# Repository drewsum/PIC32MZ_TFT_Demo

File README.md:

# PIC32MZ_TFT_Demo
Custom demo board for controlling a TFT screen using PIC32MZ

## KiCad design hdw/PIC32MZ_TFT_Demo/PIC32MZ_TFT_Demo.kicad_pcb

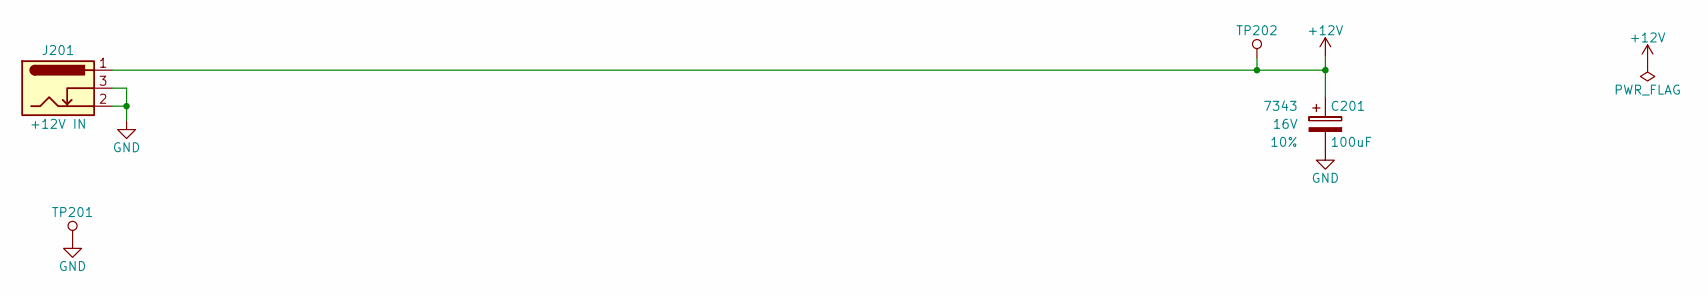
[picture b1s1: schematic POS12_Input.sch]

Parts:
C201: 100uF; CP_Tantalum_Case-X_EIA-7343-43_Reflow; Voltage 16V; Tolerance 10%; Digi-Key PN 718-1102-1-ND
J201: +12V IN; BARREL_JACK
TP201: TP; Pin_Header_Angled_1x01_Pitch2.54mm
TP202: TP; Test_Point

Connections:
+12V: C201.1, J201.1, TP202.1; also elsewhere on the board
GND: C201.2, J201.2, J201.3, TP201.1; also elsewhere on the board

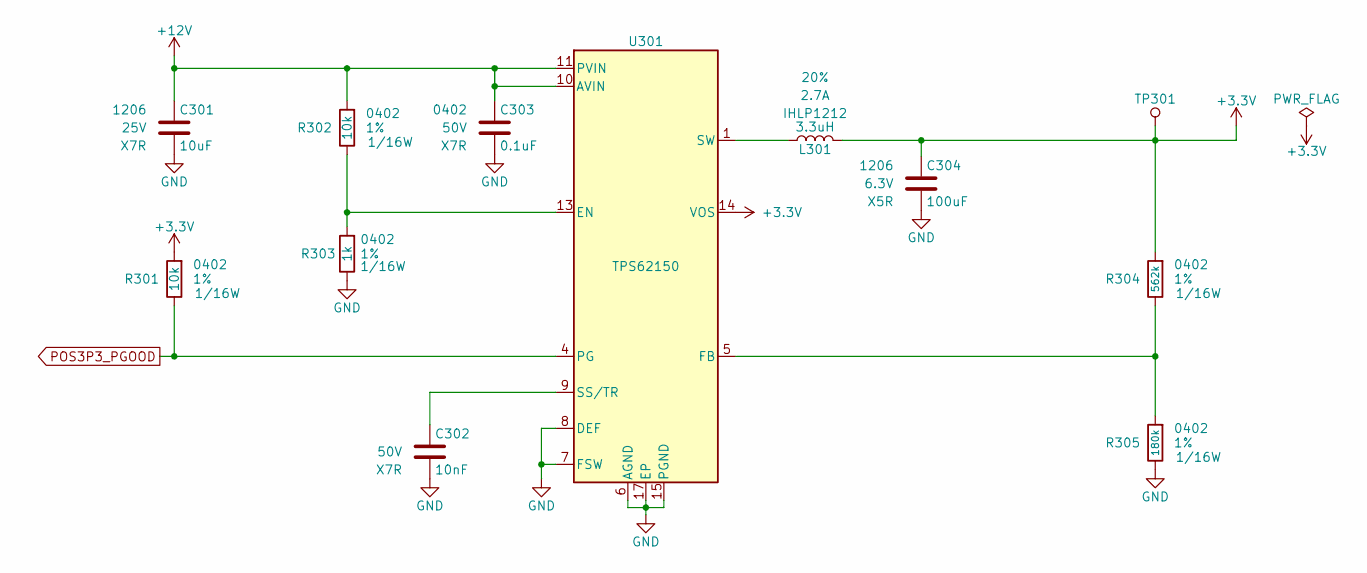
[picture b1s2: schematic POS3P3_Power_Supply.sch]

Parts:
C301: 10uF; C_1206; Voltage 25V; Digi-Key PN 1276-7031-1-ND
C302: 10nF; C_0402; Voltage 50V; Digi-Key PN 490-13295-1-ND
C303: 0.1uF; C_0402; Voltage 50V; Digi-Key PN 490-10701-1-ND
C304: 100uF; C_1206; Voltage 6.3V; Digi-Key PN 587-1963-1-ND
L301: 3.3uH; L_Vishay_IHLP-1212; Tolerance 20%; Digi-Key PN 541-2567-1-ND
R301, R302: 10k; R_0402; Tolerance 1%; Digi-Key PN RMCF0402FT10K0CT-ND
R303: 1k; R_0402; Tolerance 1%; Digi-Key PN 541-1.00KLCT-ND
R304: 562k; R_0402; Tolerance 1%; Digi-Key PN 311-562KLRCT-ND
R305: 180k; R_0402; Tolerance 1%; Digi-Key PN A129654CT-ND
TP301: TP; Test_Point
U301: TPS62150; QFN-16-1EP_3x3mm_P0.5mm_EP1.8x1.8mm; Digi-Key PN 296-41757-1-ND

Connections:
+3V3: C304.1, L301.2, R301.1, R304.1, TP301.1, U301.14 (VOS); also elsewhere on the board
+12V: C301.1, C303.1, R302.1, U301.10 (AVIN), U301.11 (PVIN), U301.12 (PVIN); also elsewhere on the board
GND: C301.2, C302.2, C303.2, C304.2, R303.2, R305.2, U301.6 (AGND), U301.7 (FSW), U301.8 (DEF), U301.15 (PGND), U301.16 (PGND), U301.17 (EP); also elsewhere on the board
unnamed: C302.1, U301.9 (SS/TR)
unnamed: L301.1, U301.1 (SW), U301.2 (SW), U301.3 (SW)
unnamed: R302.2, R303.1, U301.13 (EN)
unnamed: R304.2, R305.1, U301.5 (FB)
POS3P3_PGOOD: R301.2, U301.4 (PG); also elsewhere on the board

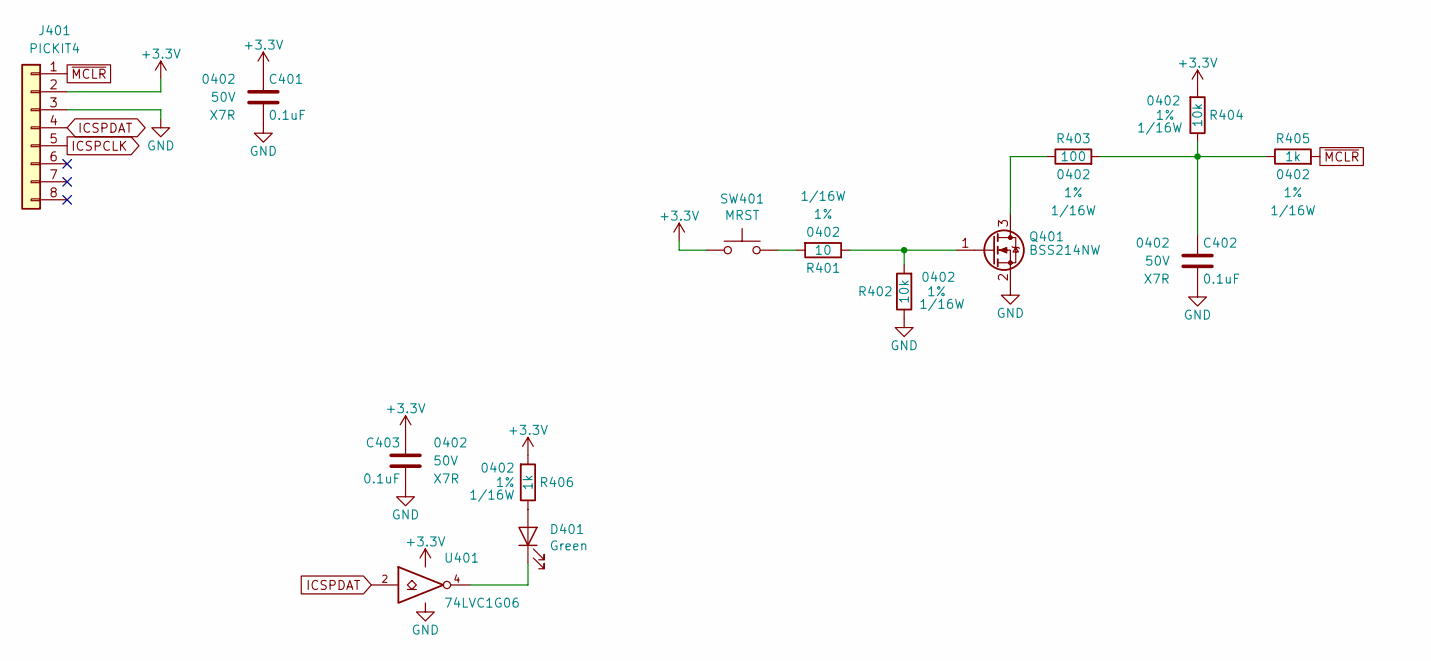
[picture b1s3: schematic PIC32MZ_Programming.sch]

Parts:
C401, C402, C403: 0.1uF; C_0402; Voltage 50V; Digi-Key PN 490-10701-1-ND
D401: Green; LED_0402; Digi-Key PN 1497-1219-1-ND
J401: PICKIT4; PICKIT4_Header
Q401: BSS214NW; SOT-323_SC-70; Digi-Key PN BSS214NWH6327XTSA1CT-ND
R401: 10; R_0402; Tolerance 1%; Digi-Key PN 541-3964-1-ND
R402, R404: 10k; R_0402; Tolerance 1%; Digi-Key PN RMCF0402FT10K0CT-ND
R403: 100; R_0402; Tolerance 1%; Digi-Key PN 541-100LCT-ND
R405, R406: 1k; R_0402; Tolerance 1%; Digi-Key PN 541-1.00KLCT-ND
SW401: MRST; SW_PUSH_6mm
U401: 74LVC1G06; SOT-353_SC-70-5; Digi-Key PN 296-8484-1-ND

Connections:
+3V3: C401.1, C403.1, J401.2, R404.1, R406.1, SW401.1, U401.5 (VCC); also elsewhere on the board
GND: C401.2, C402.2, C403.2, J401.3, Q401.2 (S), R402.2, U401.3 (GND); also elsewhere on the board
ICSPCLK: J401.5; also elsewhere on the board
ICSPDAT: J401.4, U401.2; also elsewhere on the board
unnamed: C402.1, R403.1, R404.2, R405.2
unnamed: D401.1 (K), U401.4
unnamed: D401.2 (A), R406.2
unnamed: Q401.1 (G), R401.2, R402.1
unnamed: Q401.3 (D), R403.2
unnamed: R401.1, SW401.2
~MCLR: J401.1, R405.1; also elsewhere on the board

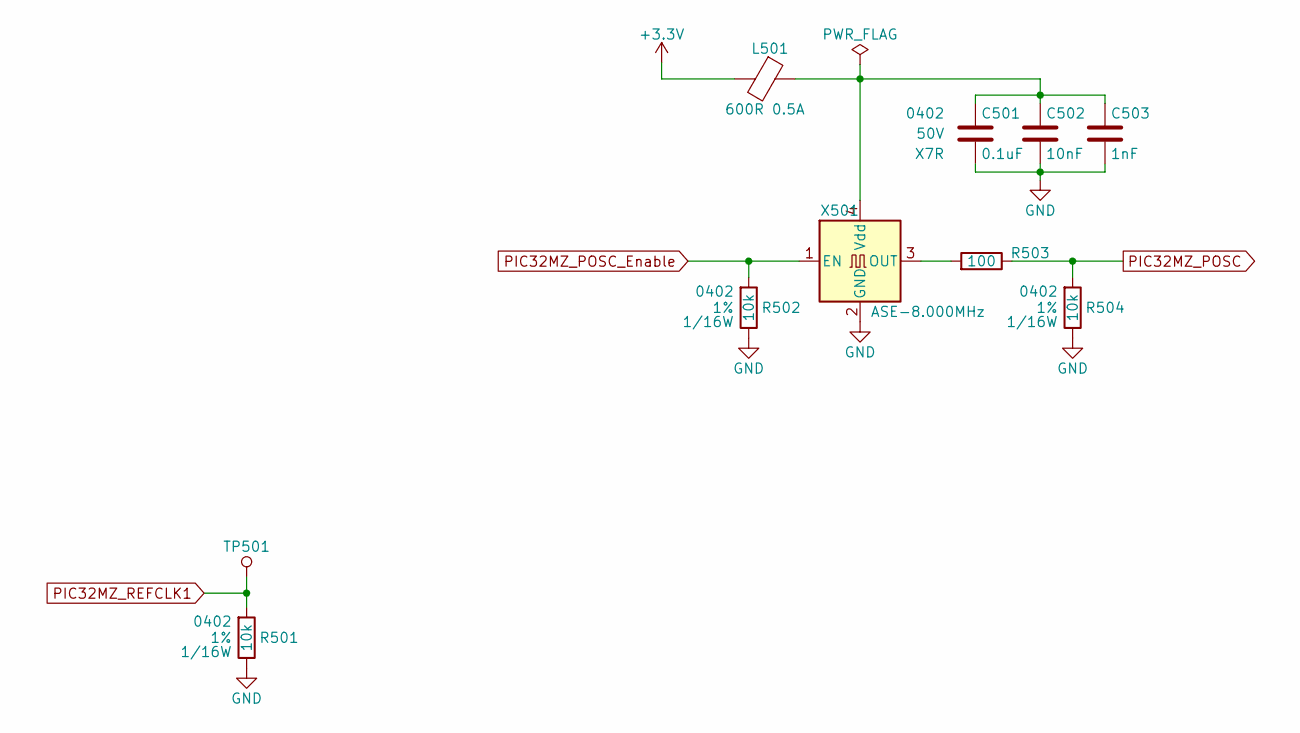
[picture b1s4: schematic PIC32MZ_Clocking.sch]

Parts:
C501: 0.1uF; C_0402; Voltage 50V; Digi-Key PN 490-10701-1-ND
C502: 10nF; C_0402; Voltage 50V; Digi-Key PN 490-13295-1-ND
C503: 1nF; C_0402; Voltage 50V; Digi-Key PN 399-1032-1-ND
L501: 600R 0.5A; L_0402; Digi-Key PN 490-5441-1-ND
R501, R502, R504: 10k; R_0402; Tolerance 1%; Digi-Key PN RMCF0402FT10K0CT-ND
R503: 100; R_0402; Tolerance 1%; Digi-Key PN 541-100LCT-ND
TP501: TP; Test_Point
X501: ASE-8.000MHz; Oscillator_SMD_Abracon_ASE-4Pin_3.2x2.5mm; Digi-Key PN 535-9558-1-ND

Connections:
+3V3: L501.2; also elsewhere on the board
GND: C501.2, C502.2, C503.2, R501.2, R502.2, R504.2, X501.2 (GND); also elsewhere on the board
unnamed: C501.1, C502.1, C503.1, L501.1, X501.4 (Vdd)
unnamed: R503.1, X501.3 (OUT)
PIC32MZ_POSC: R503.2, R504.1; also elsewhere on the board
PIC32MZ_POSC_Enable: R502.1, X501.1 (EN); also elsewhere on the board
PIC32MZ_REFCLK1: R501.1, TP501.1; also elsewhere on the board

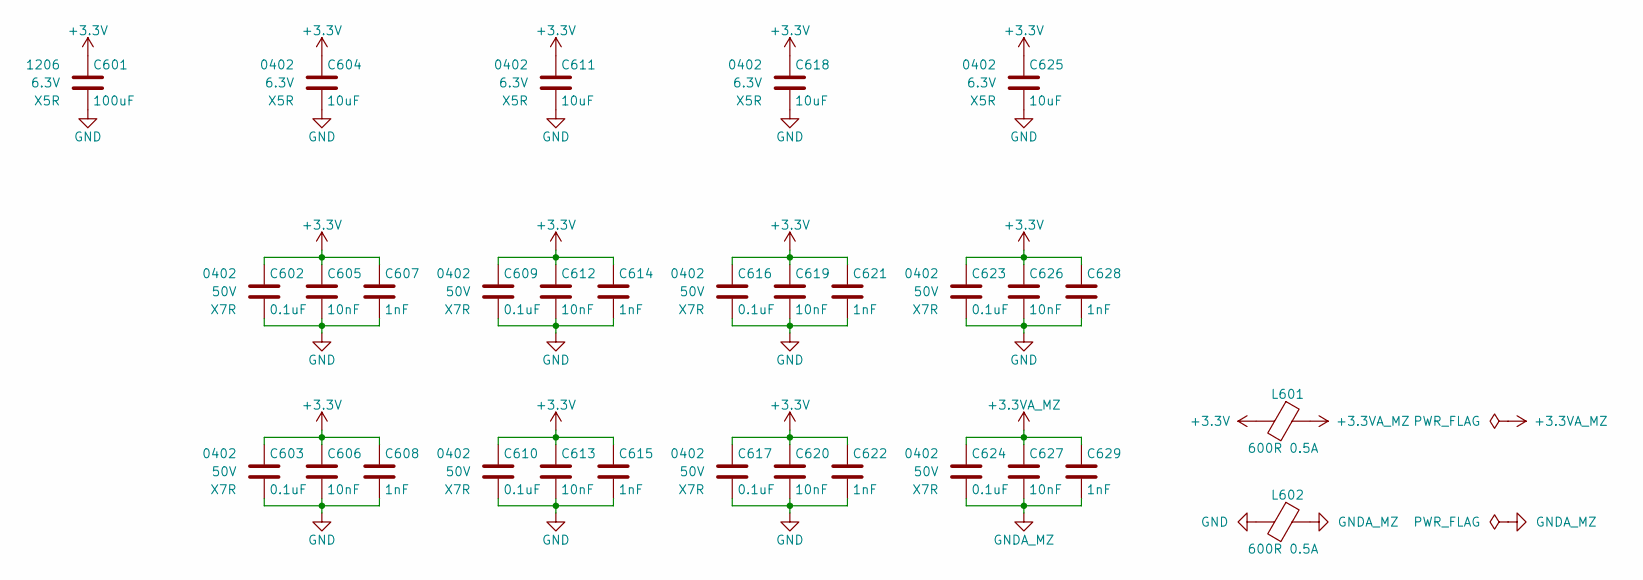
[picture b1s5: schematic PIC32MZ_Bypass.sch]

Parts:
C601: 100uF; C_1206; Voltage 6.3V; Digi-Key PN 587-1963-1-ND
C602, C603, C609, C610, C616, C617, C623, C624: 0.1uF; C_0402; Voltage 50V; Digi-Key PN 490-10701-1-ND
C604, C611, C618, C625: 10uF; C_0402; Voltage 6.3V; Digi-Key PN 490-13211-1-ND
C605, C606, C612, C613, C619, C620, C626, C627: 10nF; C_0402; Voltage 50V; Digi-Key PN 490-13295-1-ND
C607, C608, C614, C615, C621, C622, C628, C629: 1nF; C_0402; Voltage 50V; Digi-Key PN 399-1032-1-ND
L601, L602: 600R 0.5A; L_0402; Digi-Key PN 490-5441-1-ND

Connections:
+3.3VA_MZ: C624.1, C627.1, C629.1, L601.1; also elsewhere on the board
+3V3: C601.1, C602.1, C603.1, C604.1, C605.1, C606.1, C607.1, C608.1, C609.1, C610.1, C611.1, C612.1, C613.1, C614.1, C615.1, C616.1, C617.1, C618.1, C619.1, C620.1, C621.1, C622.1, C623.1, C625.1, C626.1, C628.1, L601.2; also elsewhere on the board
GND: C601.2, C602.2, C603.2, C604.2, C605.2, C606.2, C607.2, C608.2, C609.2, C610.2, C611.2, C612.2, C613.2, C614.2, C615.2, C616.2, C617.2, C618.2, C619.2, C620.2, C621.2, C622.2, C623.2, C625.2, C626.2, C628.2, L602.2; also elsewhere on the board
GNDA_MZ: C624.2, C627.2, C629.2, L602.1; also elsewhere on the board

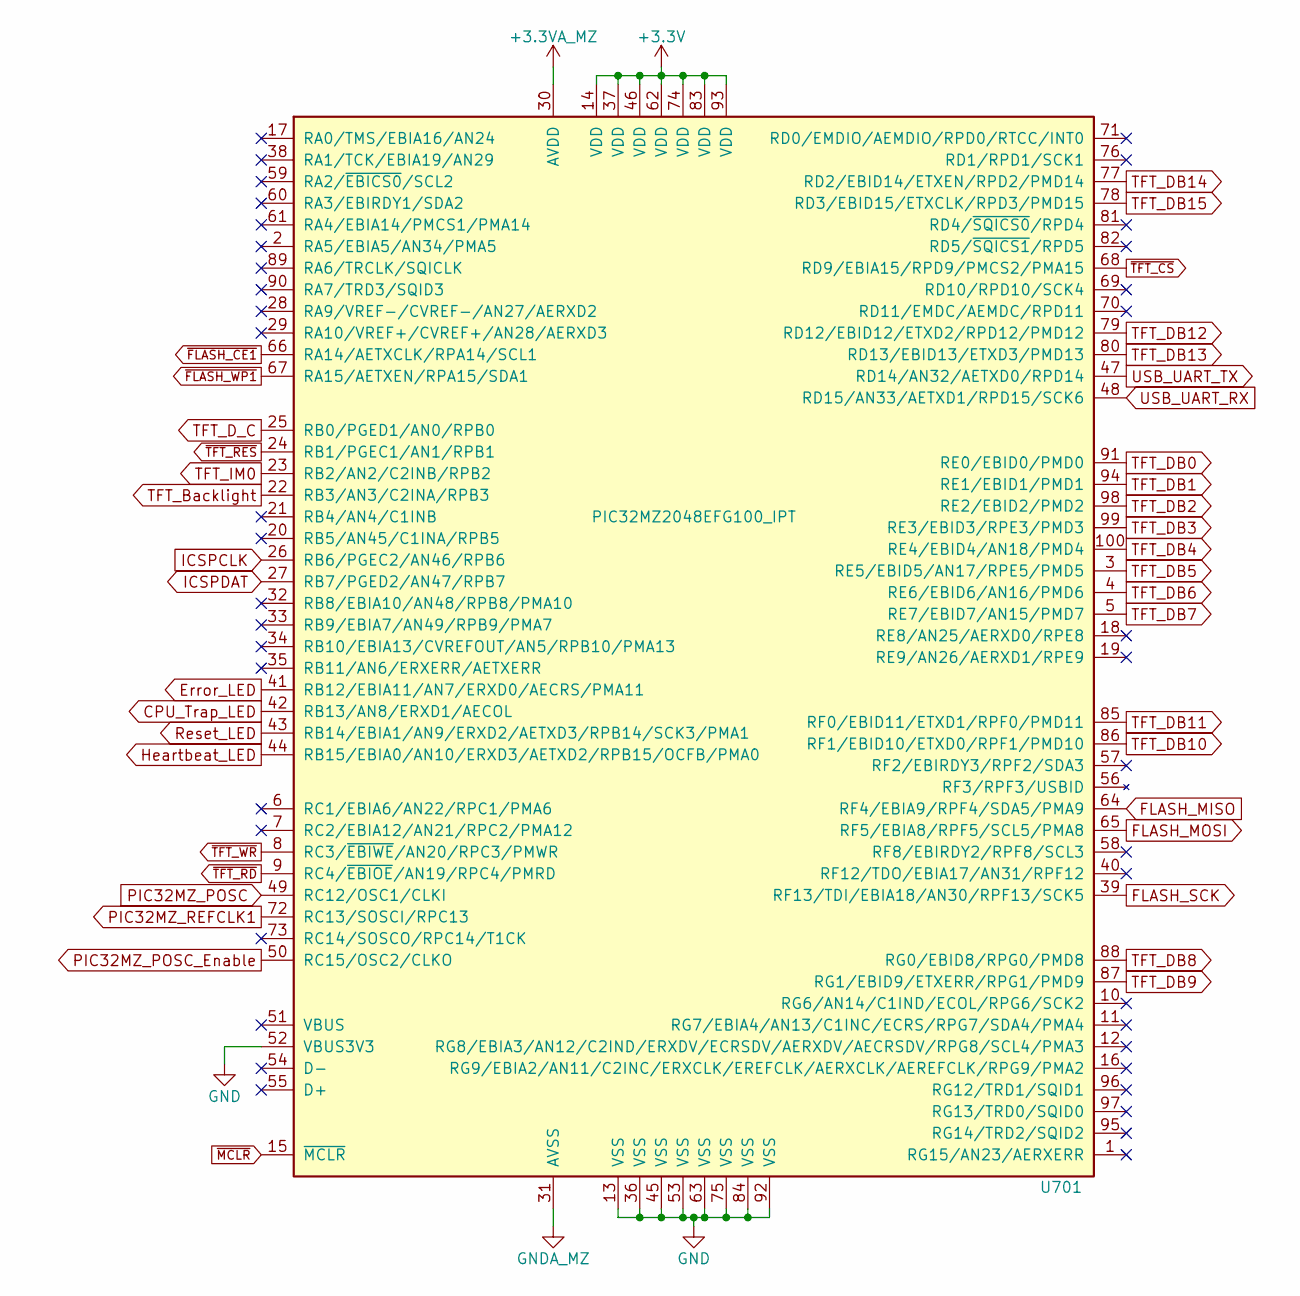
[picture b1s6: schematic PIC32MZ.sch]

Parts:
U701: PIC32MZ2048EFG100_IPT; TQFP-100_14x14mm_Pitch0.5mm; Digi-Key PN PIC32MZ2048EFH100-I/PF-ND

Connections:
+3.3VA_MZ: U701.30 (AVDD); also elsewhere on the board
+3V3: U701.14 (VDD), U701.37 (VDD), U701.46 (VDD), U701.62 (VDD), U701.74 (VDD), U701.83 (VDD), U701.93 (VDD); also elsewhere on the board
CPU_Trap_LED: U701.42 (RB13/AN8/ERXD1/AECOL); also elsewhere on the board
Error_LED: U701.41 (RB12/EBIA11/AN7/ERXD0/AECRS/PMA11); also elsewhere on the board
FLASH_MISO: U701.64 (RF4/EBIA9/RPF4/SDA5/PMA9); also elsewhere on the board
FLASH_MOSI: U701.65 (RF5/EBIA8/RPF5/SCL5/PMA8); also elsewhere on the board
FLASH_SCK: U701.39 (RF13/TDI/EBIA18/AN30/RPF13/SCK5); also elsewhere on the board
GND: U701.13 (VSS), U701.36 (VSS), U701.45 (VSS), U701.52 (VBUS3V3), U701.53 (VSS), U701.63 (VSS), U701.75 (VSS), U701.84 (VSS), U701.92 (VSS); also elsewhere on the board
GNDA_MZ: U701.31 (AVSS); also elsewhere on the board
Heartbeat_LED: U701.44 (RB15/EBIA0/AN10/ERXD3/AETXD2/RPB15/OCFB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); also elsewhere on the board
ICSPCLK: U701.26 (RB6/PGEC2/AN46/RPB6); also elsewhere on the board
ICSPDAT: U701.27 (RB7/PGED2/AN47/RPB7); also elsewhere on the board
PIC32MZ_POSC: U701.49 (RC12/OSC1/CLKI); also elsewhere on the board
PIC32MZ_POSC_Enable: U701.50 (RC15/OSC2/CLKO); also elsewhere on the board
PIC32MZ_REFCLK1: U701.72 (RC13/SOSCI/RPC13); also elsewhere on the board
Reset_LED: U701.43 (RB14/EBIA1/AN9/ERXD2/AETXD3/RPB14/SCK3/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); also elsewhere on the board
TFT_Backlight: U701.22 (RB3/AN3/C2INA/RPB3); also elsewhere on the board
TFT_DB0: U701.91 (RE0/EBID0/PMD0); also elsewhere on the board
TFT_DB1: U701.94 (RE1/EBID1/PMD1); also elsewhere on the board
TFT_DB2: U701.98 (RE2/EBID2/PMD2); also elsewhere on the board
TFT_DB3: U701.99 (RE3/EBID3/RPE3/PMD3); also elsewhere on the board
TFT_DB4: U701.100 (RE4/EBID4/AN18/PMD4); also elsewhere on the board
TFT_DB5: U701.3 (RE5/EBID5/AN17/RPE5/PMD5); also elsewhere on the board
TFT_DB6: U701.4 (RE6/EBID6/AN16/PMD6); also elsewhere on the board
TFT_DB7: U701.5 (RE7/EBID7/AN15/PMD7); also elsewhere on the board
TFT_DB8: U701.88 (RG0/EBID8/RPG0/PMD8); also elsewhere on the board
TFT_DB9: U701.87 (RG1/EBID9/ETXERR/RPG1/PMD9); also elsewhere on the board
TFT_DB10: U701.86 (RF1/EBID10/ETXD0/RPF1/PMD10); also elsewhere on the board
TFT_DB11: U701.85 (RF0/EBID11/ETXD1/RPF0/PMD11); also elsewhere on the board
TFT_DB12: U701.79 (RD12/EBID12/ETXD2/RPD12/PMD12); also elsewhere on the board
TFT_DB13: U701.80 (RD13/EBID13/ETXD3/PMD13); also elsewhere on the board
TFT_DB14: U701.77 (RD2/EBID14/ETXEN/RPD2/PMD14); also elsewhere on the board
TFT_DB15: U701.78 (RD3/EBID15/ETXCLK/RPD3/PMD15); also elsewhere on the board
TFT_D_C: U701.25 (RB0/PGED1/AN0/RPB0); also elsewhere on the board
TFT_IM0: U701.23 (RB2/AN2/C2INB/RPB2); also elsewhere on the board
USB_UART_RX: U701.48 (RD15/AN33/AETXD1/RPD15/SCK6); also elsewhere on the board
USB_UART_TX: U701.47 (RD14/AN32/AETXD0/RPD14); also elsewhere on the board
~FLASH_CE1: U701.66 (RA14/AETXCLK/RPA14/SCL1); also elsewhere on the board
~FLASH_WP1: U701.67 (RA15/AETXEN/RPA15/SDA1); also elsewhere on the board
~MCLR: U701.15 (~MCLR~); also elsewhere on the board
~TFT_CS: U701.68 (RD9/EBIA15/RPD9/PMCS2/PMA15); also elsewhere on the board
~TFT_RD: U701.9 (RC4/~EBIOE~/AN19/RPC4/PMRD); also elsewhere on the board
~TFT_RES: U701.24 (RB1/PGEC1/AN1/RPB1); also elsewhere on the board
~TFT_WR: U701.8 (RC3/~EBIWE~/AN20/RPC3/PMWR); also elsewhere on the board

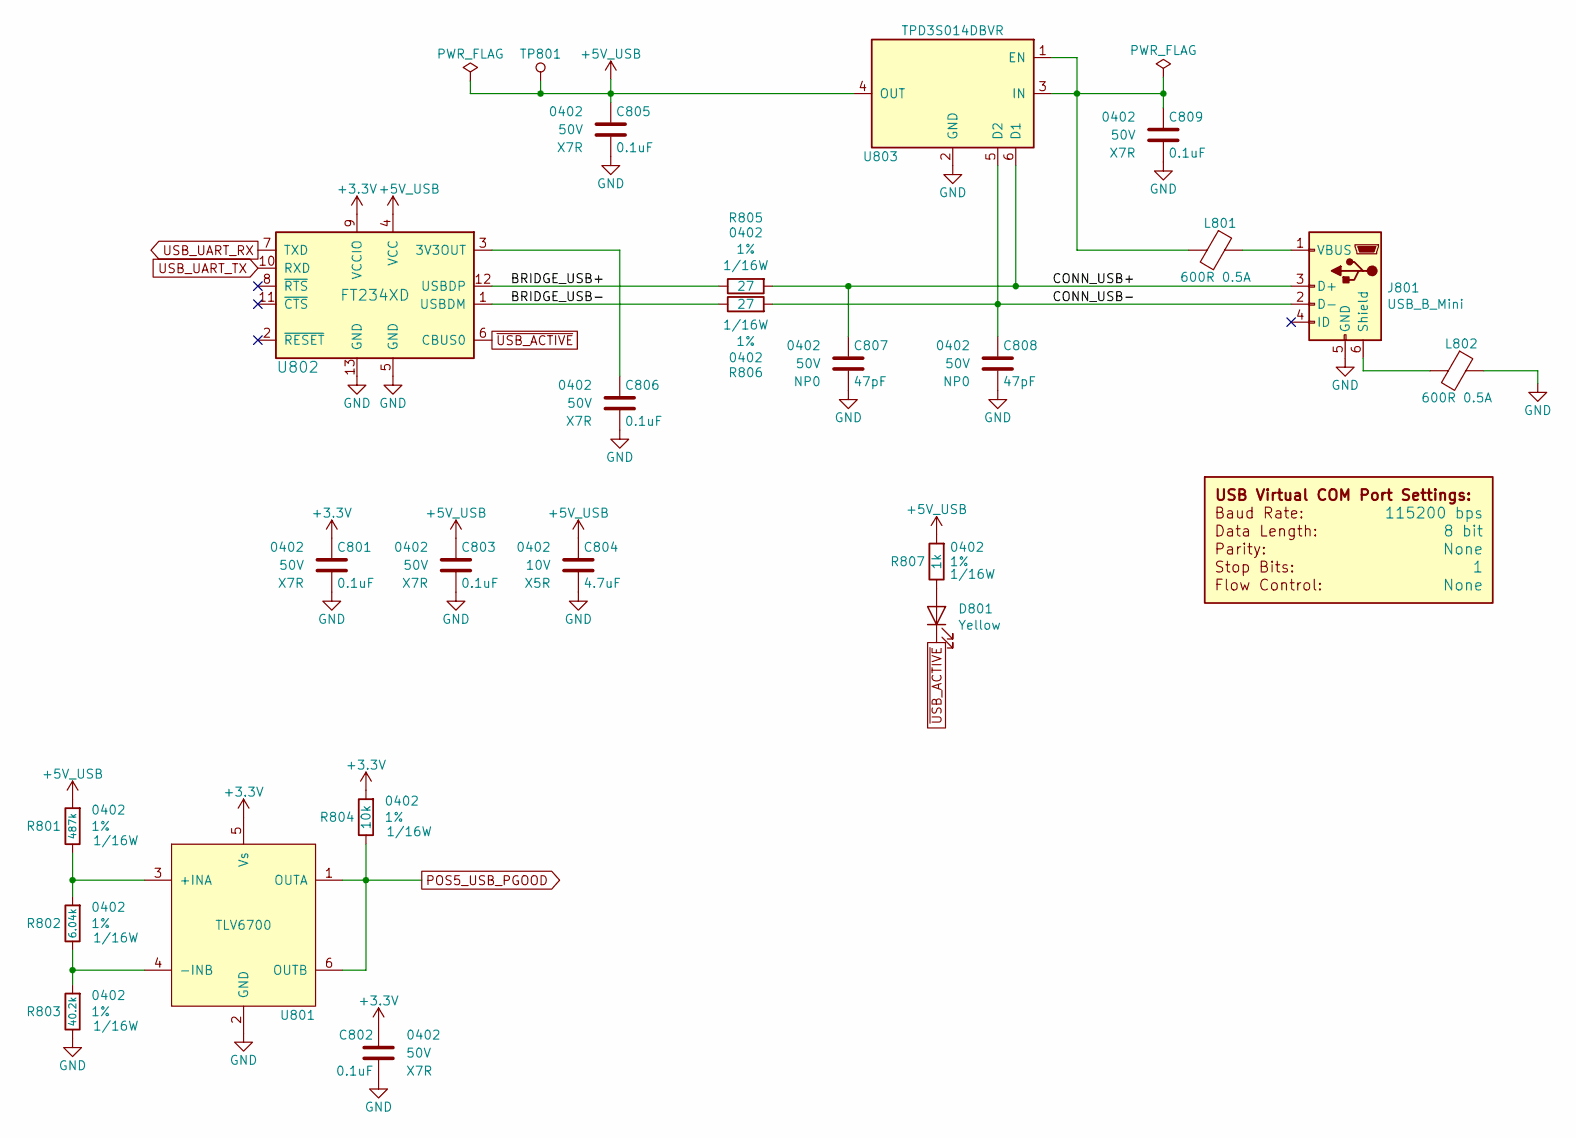
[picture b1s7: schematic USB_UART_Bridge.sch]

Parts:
C801, C802, C803, C805, C806, C809: 0.1uF; C_0402; Voltage 50V; Digi-Key PN 490-10701-1-ND
C804: 4.7uF; C_0402; Voltage 10V; Digi-Key PN 490-14306-1-ND
C807, C808: 47pF; C_0402; Voltage 50V; Digi-Key PN 399-17558-1-ND
D801: Yellow; LED_0402; Digi-Key PN 1497-1389-1-ND
DOC801: COM_Port_Settings
J801: USB_B_Mini; USB_Mini-B; Digi-Key PN 732-2109-1-ND
L801, L802: 600R 0.5A; L_0402; Digi-Key PN 490-5441-1-ND
R801: 487k; R_0402; Tolerance 1%; Digi-Key PN RMCF0402FT487KCT-ND
R802: 6.04k; R_0402; Tolerance 1%; Digi-Key PN 541-4067-1-ND
R803: 40.2k; R_0402; Tolerance 1%; Digi-Key PN 541-4097-1-ND
R804: 10k; R_0402; Tolerance 1%; Digi-Key PN RMCF0402FT10K0CT-ND
R805, R806: 27; R_0402; Tolerance 1%; Digi-Key PN 541-4082-1-ND
R807: 1k; R_0402; Tolerance 1%; Digi-Key PN 541-1.00KLCT-ND
TP801: TP; Test_Point
U801: TLV6700; SOT-23-6; Digi-Key PN 296-51696-1-ND
U802: FT234XD; DFN-12-1EP_3x3mm_Pitch0.45mm; Digi-Key PN 768-1178-1-ND
U803: TPD3S014DBVR; SOT-23-6; Digi-Key PN 296-38835-1-ND

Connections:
+3V3: C801.1, C802.1, R804.1, U801.5 (Vs), U802.9 (VCCIO); also elsewhere on the board
+5V_USB: C803.1, C804.1, C805.1, R801.1, R807.1, TP801.1, U802.4 (VCC), U803.4 (OUT)
/USB UART Bridge/BRIDGE_USB+: R805.2, U802.12 (USBDP)
/USB UART Bridge/BRIDGE_USB-: R806.2, U802.1 (USBDM)
/USB UART Bridge/CONN_USB+: C807.1, J801.3 (D+), R805.1, U803.6 (D1)
/USB UART Bridge/CONN_USB-: C808.1, J801.2 (D-), R806.1, U803.5 (D2)
GND: C801.2, C802.2, C803.2, C804.2, C805.2, C806.2, C807.2, C808.2, C809.2, J801.5 (GND), L802.1, R803.2, U801.2 (GND), U802.5 (GND), U802.13 (GND), U803.2 (GND); also elsewhere on the board
unnamed: C806.1, U802.3 (3V3OUT)
unnamed: C809.1, L801.2, U803.1 (EN), U803.3 (IN)
unnamed: D801.2 (A), R807.2
unnamed: J801.1 (VBUS), L801.1
unnamed: J801.6 (Shield), L802.2
unnamed: R801.2, R802.1, U801.3 (+INA)
unnamed: R802.2, R803.1, U801.4 (-INB)
POS5_USB_PGOOD: R804.2, U801.1 (OUTA), U801.6 (OUTB); also elsewhere on the board
USB_UART_RX: U802.7 (TXD); also elsewhere on the board
USB_UART_TX: U802.10 (RXD); also elsewhere on the board
~USB_ACTIVE: D801.1 (K), U802.6 (CBUS0)

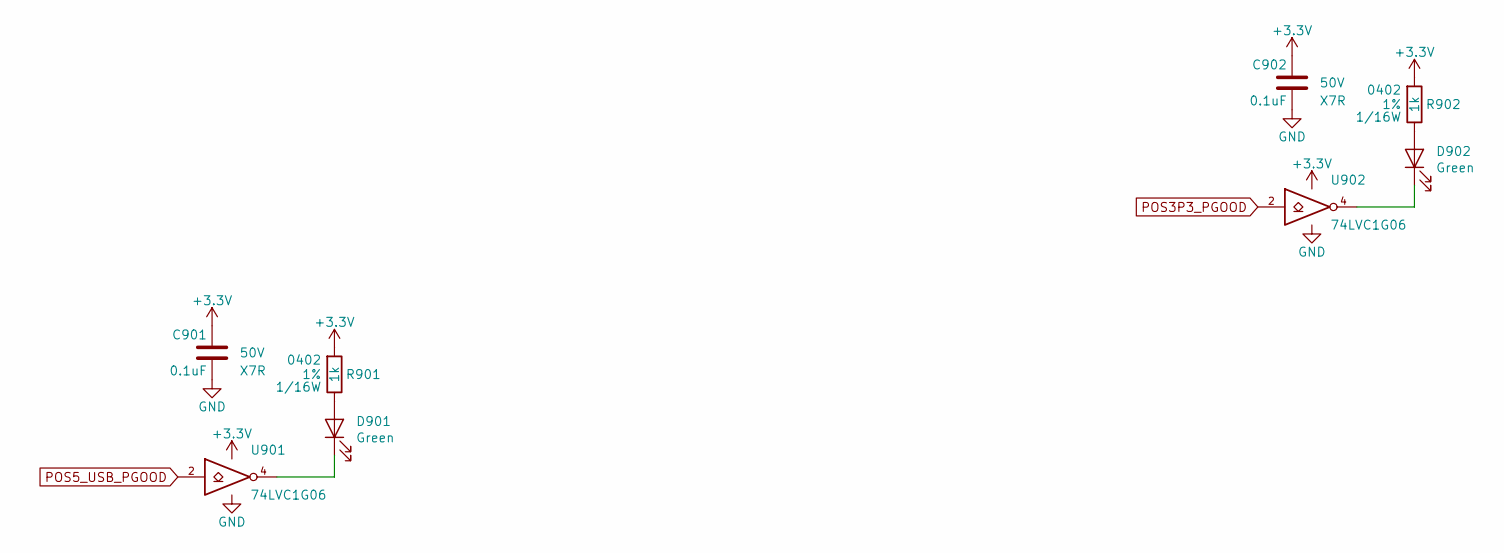
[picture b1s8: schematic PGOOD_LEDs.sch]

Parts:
C901, C902: 0.1uF; C_0402; Voltage 50V; Digi-Key PN 490-10701-1-ND
D901, D902: Green; LED_0402; Digi-Key PN 1497-1219-1-ND
R901, R902: 1k; R_0402; Tolerance 1%; Digi-Key PN 541-1.00KLCT-ND
U901, U902: 74LVC1G06; SOT-353_SC-70-5; Digi-Key PN 296-8484-1-ND

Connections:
+3V3: C901.1, C902.1, R901.1, R902.1, U901.5 (VCC), U902.5 (VCC); also elsewhere on the board
GND: C901.2, C902.2, U901.3 (GND), U902.3 (GND); also elsewhere on the board
unnamed: D901.1 (K), U901.4
unnamed: D901.2 (A), R901.2
unnamed: D902.1 (K), U902.4
unnamed: D902.2 (A), R902.2
POS3P3_PGOOD: U902.2; also elsewhere on the board
POS5_USB_PGOOD: U901.2; also elsewhere on the board

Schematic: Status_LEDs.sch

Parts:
C1001, C1002, C1003, C1004: 0.1uF; C_0402; Voltage 50V; Digi-Key PN 490-10701-1-ND
D1001: Green; LED_0402; Digi-Key PN 1497-1219-1-ND
D1002, D1003, D1004: Red; LED_0402; Digi-Key PN 1497-1174-1-ND
R1001, R1002, R1005, R1006: 10k; R_0402; Tolerance 1%; Digi-Key PN RMCF0402FT10K0CT-ND
R1003, R1004, R1007, R1008: 1k; R_0402; Tolerance 1%; Digi-Key PN 541-1.00KLCT-ND
U1001, U1002, U1003, U1004: 74LVC1G06; SOT-353_SC-70-5; Digi-Key PN 296-8484-1-ND

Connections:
+3V3: C1001.1, C1002.1, C1003.1, C1004.1, R1003.1, R1004.1, R1005.1, R1007.1, R1008.1, U1001.5 (VCC), U1002.5 (VCC), U1003.5 (VCC), U1004.5 (VCC); also elsewhere on the board
CPU_Trap_LED: R1006.1, U1004.2; also elsewhere on the board
Error_LED: R1002.1, U1002.2; also elsewhere on the board
GND: C1001.2, C1002.2, C1003.2, C1004.2, R1001.2, R1002.2, R1006.2, U1001.3 (GND), U1002.3 (GND), U1003.3 (GND), U1004.3 (GND); also elsewhere on the board
Heartbeat_LED: R1001.1, U1001.2; also elsewhere on the board
unnamed: D1001.1 (K), U1001.4
unnamed: D1001.2 (A), R1003.2
unnamed: D1002.1 (K), U1002.4
unnamed: D1002.2 (A), R1004.2
unnamed: D1003.1 (K), U1003.4
unnamed: D1003.2 (A), R1007.2
unnamed: D1004.1 (K), U1004.4
unnamed: D1004.2 (A), R1008.2
Reset_LED: R1005.2, U1003.2; also elsewhere on the board

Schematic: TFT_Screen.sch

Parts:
C1101, C1106: 10uF; C_0402; Voltage 6.3V; Digi-Key PN 490-13211-1-ND
C1102, C1103: 0.1uF; C_0402; Voltage 50V; Digi-Key PN 490-10701-1-ND
C1104: 10nF; C_0402; Voltage 50V; Digi-Key PN 490-13295-1-ND
C1105: 1nF; C_0402; Voltage 50V; Digi-Key PN 399-1032-1-ND
J1101: TFT FFC; MOLEX_0541324062; Digi-Key PN WM3436CT-ND
N1101: NHD-2.4-240320CF-CSXV#-F; Digi-Key PN NHD-2.4-240320CF-CSXV#-F-ND
R1101, R1102, R1107, R1108, R1109, R1110, R1111: 10k; R_0402; Tolerance 1%; Digi-Key PN RMCF0402FT10K0CT-ND
R1103, R1104, R1105, R1106: 10; R_0402; Tolerance 1%; Digi-Key PN 541-3964-1-ND
RN1101, RN1102: 10; R_Array_Convex_8x0602; Digi-Key PN Y1100CT-ND
RN1103, RN1104: 10k; R_Array_Convex_8x0602; Digi-Key PN Y1103CT-ND
U1101: SiP32431DR3; SOT-363_SC-70-6; Digi-Key PN SIP32431DR3-T1GE3CT-ND

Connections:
+3.3V_TFT: C1103.1, J1101.38, U1101.1 (OUT)
+3V3: C1101.1, C1102.1, C1104.1, C1105.1, C1106.1, J1101.7, J1101.8, R1108.1, R1109.1, R1110.1, U1101.4 (IN); also elsewhere on the board
GND: C1101.2, C1102.2, C1103.2, C1104.2, C1105.2, C1106.2, J1101.1, J1101.33, J1101.34, J1101.35, J1101.36, J1101.37, J1101.39, R1101.2, R1102.2, R1107.2, R1111.2, RN1103.1 (R1.1), RN1103.2 (R2.1), RN1103.3 (R3.1), RN1103.4 (R4.1), RN1103.5 (R5.1), RN1103.6 (R6.1), RN1103.7 (R7.1), RN1103.8 (R8.1), RN1104.1 (R1.1), RN1104.2 (R2.1), RN1104.3 (R3.1), RN1104.4 (R4.1), RN1104.5 (R5.1), RN1104.6 (R6.1), RN1104.7 (R7.1), RN1104.8 (R8.1), U1101.2 (GND), U1101.5 (GND); also elsewhere on the board
unnamed: J1101.10, R1103.2, R1110.2
unnamed: J1101.11, R1104.2, R1111.1
unnamed: J1101.12, R1105.2, R1109.2
unnamed: J1101.13, R1106.2, R1108.2
unnamed: J1101.14, RN1101.9 (R8.2), RN1104.9 (R8.2)
unnamed: J1101.15, RN1101.10 (R7.2), RN1104.10 (R7.2)
unnamed: J1101.16, RN1101.11 (R6.2), RN1104.11 (R6.2)
unnamed: J1101.17, RN1101.12 (R5.2), RN1104.12 (R5.2)
unnamed: J1101.18, RN1101.13 (R4.2), RN1104.13 (R4.2)
unnamed: J1101.19, RN1101.14 (R3.2), RN1104.14 (R3.2)
unnamed: J1101.20, RN1101.15 (R2.2), RN1104.15 (R2.2)
unnamed: J1101.21, RN1101.16 (R1.2), RN1104.16 (R1.2)
unnamed: J1101.22, RN1102.9 (R8.2), RN1103.9 (R8.2)
unnamed: J1101.23, RN1102.10 (R7.2), RN1103.10 (R7.2)
unnamed: J1101.24, RN1102.11 (R6.2), RN1103.11 (R6.2)
unnamed: J1101.25, RN1102.12 (R5.2), RN1103.12 (R5.2)
unnamed: J1101.26, RN1102.13 (R4.2), RN1103.13 (R4.2)
unnamed: J1101.27, RN1102.14 (R3.2), RN1103.14 (R3.2)
unnamed: J1101.28, RN1102.15 (R2.2), RN1103.15 (R2.2)
unnamed: J1101.29, RN1102.16 (R1.2), RN1103.16 (R1.2)
TFT_Backlight: R1107.1, U1101.3 (ON); also elsewhere on the board
TFT_DB0: RN1101.8 (R8.1); also elsewhere on the board
TFT_DB1: RN1101.7 (R7.1); also elsewhere on the board
TFT_DB2: RN1101.6 (R6.1); also elsewhere on the board
TFT_DB3: RN1101.5 (R5.1); also elsewhere on the board
TFT_DB4: RN1101.4 (R4.1); also elsewhere on the board
TFT_DB5: RN1101.3 (R3.1); also elsewhere on the board
TFT_DB6: RN1101.2 (R2.1); also elsewhere on the board
TFT_DB7: RN1101.1 (R1.1); also elsewhere on the board
TFT_DB8: RN1102.8 (R8.1); also elsewhere on the board
TFT_DB9: RN1102.7 (R7.1); also elsewhere on the board
TFT_DB10: RN1102.6 (R6.1); also elsewhere on the board
TFT_DB11: RN1102.5 (R5.1); also elsewhere on the board
TFT_DB12: RN1102.4 (R4.1); also elsewhere on the board
TFT_DB13: RN1102.3 (R3.1); also elsewhere on the board
TFT_DB14: RN1102.2 (R2.1); also elsewhere on the board
TFT_DB15: RN1102.1 (R1.1); also elsewhere on the board
TFT_D_C: R1104.1; also elsewhere on the board
TFT_IM0: J1101.31, R1101.1; also elsewhere on the board
~TFT_CS: R1103.1; also elsewhere on the board
~TFT_RD: R1106.1; also elsewhere on the board
~TFT_RES: J1101.30, R1102.1; also elsewhere on the board
~TFT_WR: R1105.1; also elsewhere on the board

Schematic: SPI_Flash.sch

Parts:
C1201, C1202: 0.1uF; C_0402; Voltage 50V; Digi-Key PN 490-10701-1-ND
C1203: 10nF; C_0402; Voltage 50V; Digi-Key PN 490-13295-1-ND
C1204: 1nF; C_0402; Voltage 50V; Digi-Key PN 399-1032-1-ND
D1201: Green; LED_0402; Digi-Key PN 1497-1219-1-ND
R1201: 1k; R_0402; Tolerance 1%; Digi-Key PN 541-1.00KLCT-ND
R1202, R1203, R1204, R1205, R1212: 10; R_0402; Tolerance 1%; Digi-Key PN 541-3964-1-ND
R1206, R1207, R1208, R1209, R1210, R1211: 10k; R_0402; Tolerance 1%; Digi-Key PN RMCF0402FT10K0CT-ND
U1201: 74LVC1G07; SOT-353_SC-70-5; Digi-Key PN 296-8486-1-ND
U1202: SST25VF080B-50-4I-S2AF; SOIC-8_5.275x5.275mm_P1.27mm; Digi-Key PN SST25VF080B-50-4I-S2AF-T

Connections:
+3V3: C1201.1, C1202.1, C1203.1, C1204.1, R1201.1, R1208.1, R1209.1, R1210.1, U1201.5 (VCC), U1202.8 (VDD); also elsewhere on the board
FLASH_MISO: R1212.2; also elsewhere on the board
FLASH_MOSI: R1202.2; also elsewhere on the board
FLASH_SCK: R1203.2; also elsewhere on the board
GND: C1201.2, C1202.2, C1203.2, C1204.2, R1206.2, R1207.2, R1211.2, U1201.3 (GND), U1202.4 (VSS); also elsewhere on the board
unnamed: D1201.1 (K), U1201.4
unnamed: D1201.2 (A), R1201.2
unnamed: R1202.1, R1206.1, U1202.5 (SI)
unnamed: R1203.1, R1207.1, U1202.6 (SCK)
unnamed: R1204.1, R1208.2, U1202.1 (~CE)
unnamed: R1205.1, R1209.2, U1202.3 (~WP~)
unnamed: R1210.2, U1202.7 (~HOLD~)
unnamed: R1211.1, R1212.1, U1202.2 (SO)
~FLASH_CE1: R1204.2, U1201.2; also elsewhere on the board
~FLASH_WP1: R1205.2; also elsewhere on the board

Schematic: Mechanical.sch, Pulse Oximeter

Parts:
H2301, H2302, H2303, H2304: MountingHole; MountingHole_3mm
MK2301, MK2302, MK2305, MK2306: Standoff; Digi-Key PN 1772-1220-ND
MK2303, MK2304, MK2307, MK2308: Screw; Digi-Key PN 36-9900-ND

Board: 2 copper layers, 170 parts (21 on the bottom side), 113 nets, no tracks yet.

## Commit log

2020-06-12 gitignoring
2020-06-12 started kicad project
2020-06-13 Added TFT screen sch sheet
2020-07-04 Started PCB layout
2020-07-05 More board part arrangement
